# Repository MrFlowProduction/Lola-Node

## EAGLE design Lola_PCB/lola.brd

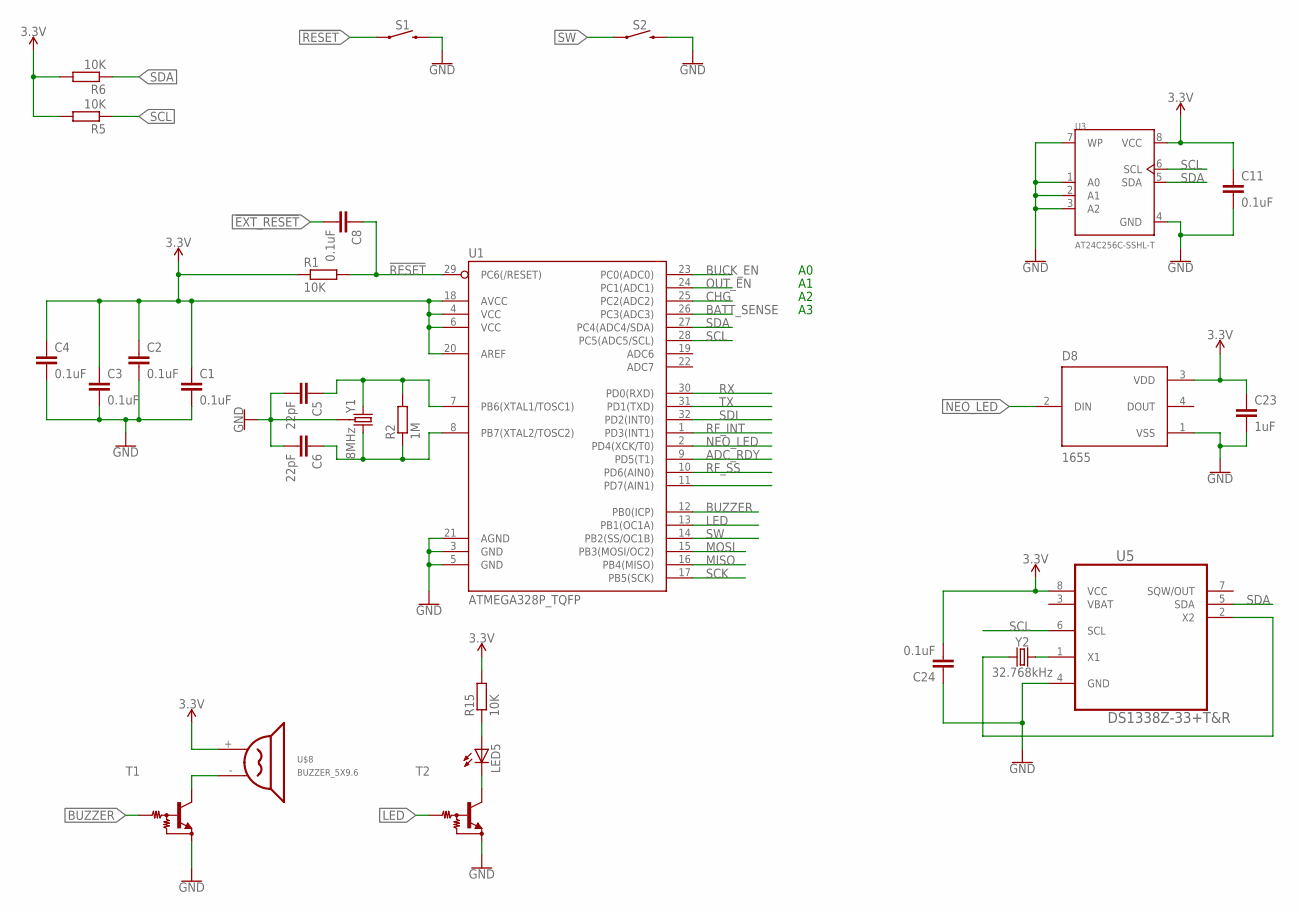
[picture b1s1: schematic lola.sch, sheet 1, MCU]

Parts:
C1, C2, C3, C4, C8, C11, C24: 0.1uF; C0603
C5, C6: 22pF; C0603
C23: 1uF; C0603
D8: 1655; LED_1655
LED5: LEDCHIPLED_0805; CHIPLED_0805
R1, R5, R6, R15: 10K; R0603
R2: 1M; R0603
S1, S2: MOMENTARY-SWITCH-SPST-SMD-4.6X2.8MM; TACTILE_SWITCH_SMD_4.6X2.8MM
T1, T2: MUN2211T1-NPN_DRIVER-SC59-BEC; SC59-BEC
U1: ATMEGA328P_TQFP; TQFP32-08
U3: AT24C256C-SSHL-T; SOIC127P600X175-8N
U5: DS1338Z-33+T&R; SOIC127P600X175-8N
U$8: BUZZER_5X9.6
Y1: 8MHz; CRYSTAL-SMD-5X3.2-4PAD
Y2: 32.768kHz; CRYSTAL-SMD-3.2X1.5MM

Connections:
3.3V: C1.1, C2.1, C3.1, C4.1, C11.1, C23.1, C24.2, D8.3 (VDD), R1.1, R5.2, R6.2, R15.2, U1.4 (VCC), U1.6 (VCC), U1.18 (AVCC), U1.20 (AREF), U3.8 (VCC), U5.8 (VCC), U$8.+ (VCC); also elsewhere on the board
!EXT_RESET: C8.2; also elsewhere on the board
!RESET: C8.1, R1.2, S1.1, S1.2 (1), U1.29 (PC6(/RESET)); also elsewhere on the board
ADC_RDY: U1.9 (PD5(T1)); also elsewhere on the board
BATT_SENSE: U1.26 (PC3(ADC3)); also elsewhere on the board
BUCK_EN: U1.23 (PC0(ADC0)); also elsewhere on the board
BUZZER: T1.B, U1.12 (PB0(ICP))
CHG: U1.25 (PC2(ADC2)); also elsewhere on the board
GND: C1.2, C2.2, C3.2, C4.2, C5.2, C6.2, C11.2, C23.2, C24.1, D8.1 (VSS), S1.3 (2), S1.4 (2), S2.3 (2), S2.4 (2), T1.E, T2.E, U1.3 (GND), U1.5 (GND), U1.21 (AGND), U3.1 (A0), U3.2 (A1), U3.3 (A2), U3.4 (GND), U3.7 (WP), U5.4 (GND), Y1.2 (3), Y1.4 (3); also elsewhere on the board
LED: T2.B, U1.13 (PB1(OC1A))
MISO: U1.16 (PB4(MISO)); also elsewhere on the board
MOSI: U1.15 (PB3(MOSI/OC2)); also elsewhere on the board
unnamed: LED5.A, R15.1
unnamed: U5.1 (X1), Y2.P$2 (2)
unnamed: U5.2 (X2), Y2.P$1 (1)
unnamed: LED5.C, T2.C
unnamed: T1.C, U$8.- (GND)
unnamed: C5.1, R2.2, U1.7 (PB6(XTAL1/TOSC1)), Y1.3 (1)
unnamed: C6.1, R2.1, U1.8 (PB7(XTAL2/TOSC2)), Y1.1 (2)
NEO_LED: D8.2 (DIN), U1.2 (PD4(XCK/T0))
OUT_EN: U1.24 (PC1(ADC1)); also elsewhere on the board
RF_INT: U1.1 (PD3(INT1)); also elsewhere on the board
RF_SS: U1.10 (PD6(AIN0)); also elsewhere on the board
RX: U1.30 (PD0(RXD)); also elsewhere on the board
SCK: U1.17 (PB5(SCK)); also elsewhere on the board
SCL: R5.1, U1.28 (PC5(ADC5/SCL)), U3.6 (SCL), U5.6 (SCL); also elsewhere on the board
SDA: R6.1, U1.27 (PC4(ADC4/SDA)), U3.5 (SDA), U5.5 (SDA); also elsewhere on the board
SDI: U1.32 (PD2(INT0)); also elsewhere on the board
SW: S2.1, S2.2 (1), U1.14 (PB2(SS/OC1B))
TX: U1.31 (PD1(TXD)); also elsewhere on the board
VBAT: U5.3 (VBAT)

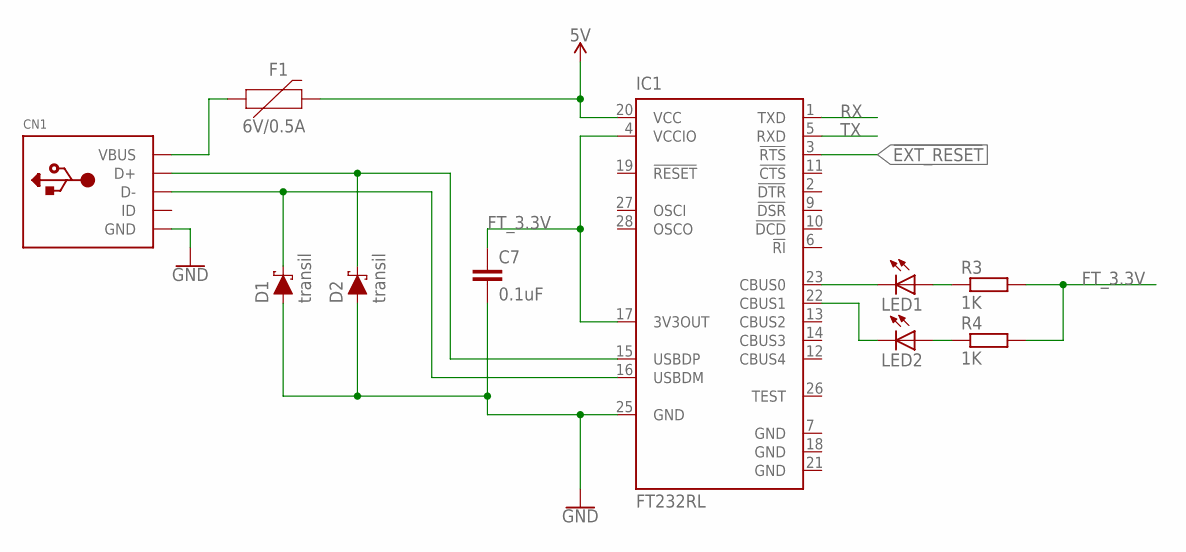
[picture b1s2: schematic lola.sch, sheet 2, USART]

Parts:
C7: 0.1uF; C0603
CN1: USBMINIB; USB-MINIB
D1, D2: transil; SOD-323
F1: 6V/0.5A; 1206
IC1: FT232RL; SSOP28
LED1, LED2: LEDCHIPLED_0805; CHIPLED_0805
R3, R4: 1K; R0603

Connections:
5V: F1.2, IC1.20 (VCC); also elsewhere on the board
!EXT_RESET: IC1.3 (!RTS); also elsewhere on the board
FT_3.3V: C7.1, IC1.4 (VCCIO), IC1.17 (3V3OUT), R3.2, R4.2
GND: C7.2, CN1.GND, D1.A, D2.A, IC1.7 (GND), IC1.18 (GND), IC1.21 (GND), IC1.25 (GND); also elsewhere on the board
unnamed: CN1.VBUS, F1.1
unnamed: CN1.D+, D2.C, IC1.15 (USBDP)
unnamed: CN1.D-, D1.C, IC1.16 (USBDM)
unnamed: LED2.A, R4.1
unnamed: IC1.22 (CBUS1), LED2.C
unnamed: IC1.23 (CBUS0), LED1.C
unnamed: LED1.A, R3.1
RX: IC1.1 (TXD); also elsewhere on the board
TX: IC1.5 (RXD); also elsewhere on the board

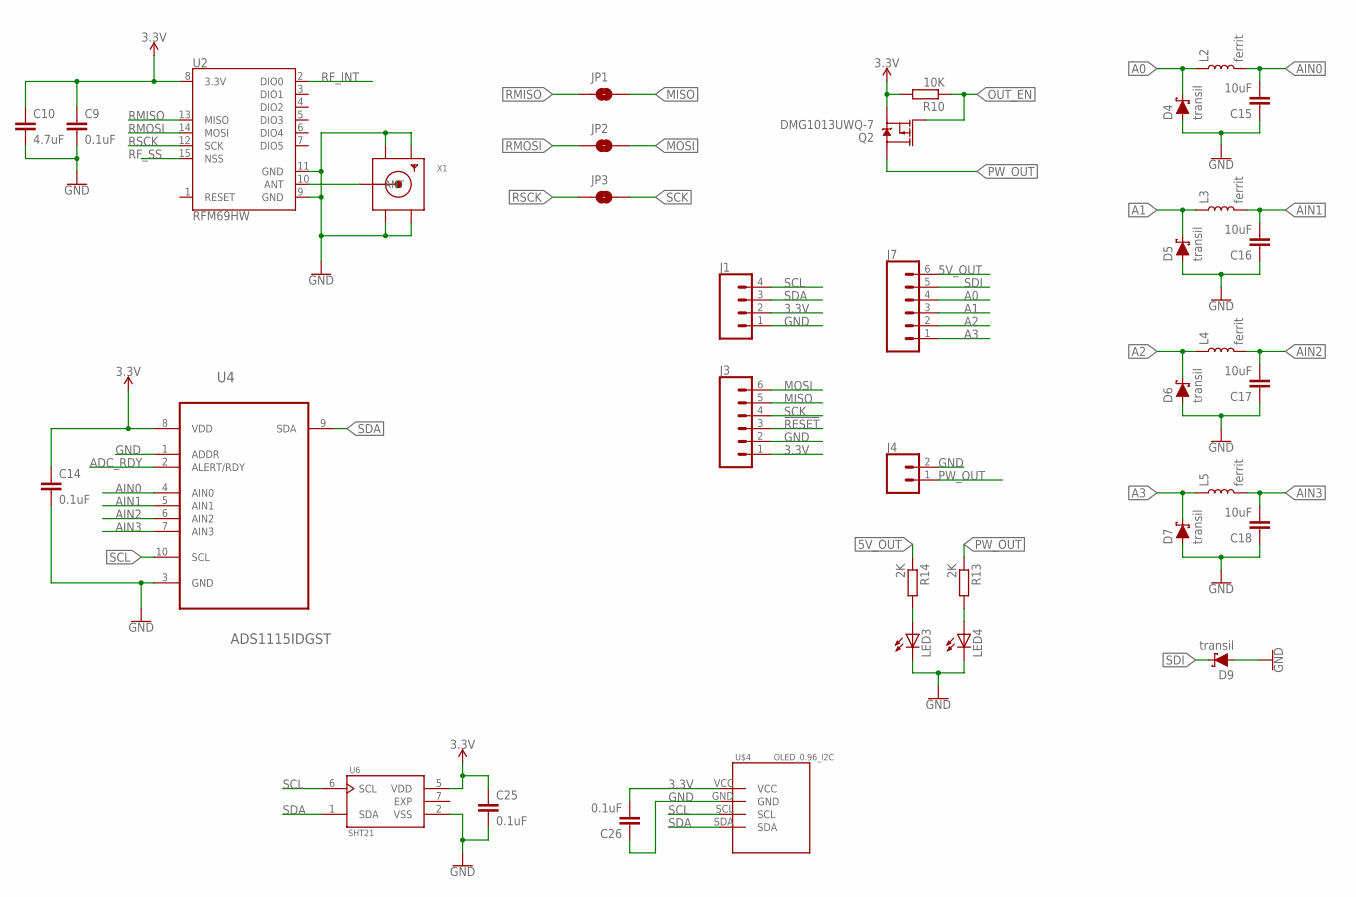
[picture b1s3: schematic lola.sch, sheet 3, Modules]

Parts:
C9, C14, C25, C26: 0.1uF; C0603
C10: 4.7uF; C0603
C15, C16, C17, C18: 10uF; C0603
D4, D5, D6, D7, D9: transil; SOD-323
J1: CONN_04LOCK_LONGPADS; 1X04_LOCK_LONGPADS
J3: CONN_06NO_SILK_FEMALE_PTH; 1X06_NO_SILK
J4: CONN_025MM; SCREWTERMINAL-5MM-2
J7: CONN_063.5MM-6; SCREWTERMINAL-3.5MM-6
JP1, JP2, JP3: JUMPER-SMT_2_NO_NO-SILK; SMT-JUMPER_2_NO_NO-SILK
L2, L3, L4, L5: ferrit; 0603
LED3, LED4: LEDCHIPLED_0805; CHIPLED_0805
Q2: DMG1013UWQ-7; SOT23-3
R10: 10K; R0603
R13, R14: 2K; R0603
U2: RFM69HW; RFM69W-XXXS2
U4: ADS1115IDGST; SOP50P490X110-10N
U6: SHT21; SON100P300X300X110-7N
U$4: OLED_0.96_I2C
X1: SMACONNECTOR_EDGE_UFL; SMA_EDGELAUNCH_UFL

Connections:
3.3V: C9.1, C10.1, C14.1, C25.1, C26.2, J1.2, J3.1, Q2.2 (S), R10.2, U2.8 (3.3V), U4.8 (VDD), U6.5 (VDD), U$4.VCC; also elsewhere on the board
5V_OUT: J7.6, R14.1; also elsewhere on the board
!RESET: J3.3; also elsewhere on the board
A0: D4.C, J7.4, L2.1
A1: D5.C, J7.3, L3.1
A2: D6.C, J7.2, L4.1
A3: D7.C, J7.1, L5.1
ADC_RDY: U4.2 (ALERT/RDY); also elsewhere on the board
AIN0: C15.2, L2.2, U4.4 (AIN0)
AIN1: C16.2, L3.2, U4.5 (AIN1)
AIN2: C17.2, L4.2, U4.6 (AIN2)
AIN3: C18.2, L5.2, U4.7 (AIN3)
EXP: U6.7 (EXP)
GND: C9.2, C10.2, C14.2, C15.1, C16.1, C17.1, C18.1, C25.2, C26.1, D4.A, D5.A, D6.A, D7.A, D9.A, J1.1, J3.2, J4.2, LED3.C, LED4.C, U2.9 (GND), U2.11 (GND), U4.1 (ADDR), U4.3 (GND), U6.2 (VSS), U$4.GND, X1.GND@1 (GND1), X1.GND@2 (GND2), X1.GND@3 (GND3), X1.GND@4 (GND4); also elsewhere on the board
MISO: J3.5, JP1.2; also elsewhere on the board
MOSI: J3.6, JP2.2; also elsewhere on the board
unnamed: U2.10 (ANT), X1.P (ANT)
unnamed: LED3.A, R14.2
unnamed: LED4.A, R13.2
OUT_EN: Q2.1 (G), R10.1; also elsewhere on the board
PW_OUT: J4.1, Q2.3 (D), R13.1
RF_INT: U2.2 (DIO0); also elsewhere on the board
RF_SS: U2.15 (NSS); also elsewhere on the board
RMISO: JP1.1, U2.13 (MISO)
RMOSI: JP2.1, U2.14 (MOSI)
RSCK: JP3.1, U2.12 (SCK)
SCK: J3.4, JP3.2; also elsewhere on the board
SCL: J1.4, U4.10 (SCL), U6.6 (SCL), U$4.SCL; also elsewhere on the board
SDA: J1.3, U4.9 (SDA), U6.1 (SDA), U$4.SDA; also elsewhere on the board
SDI: D9.C, J7.5; also elsewhere on the board

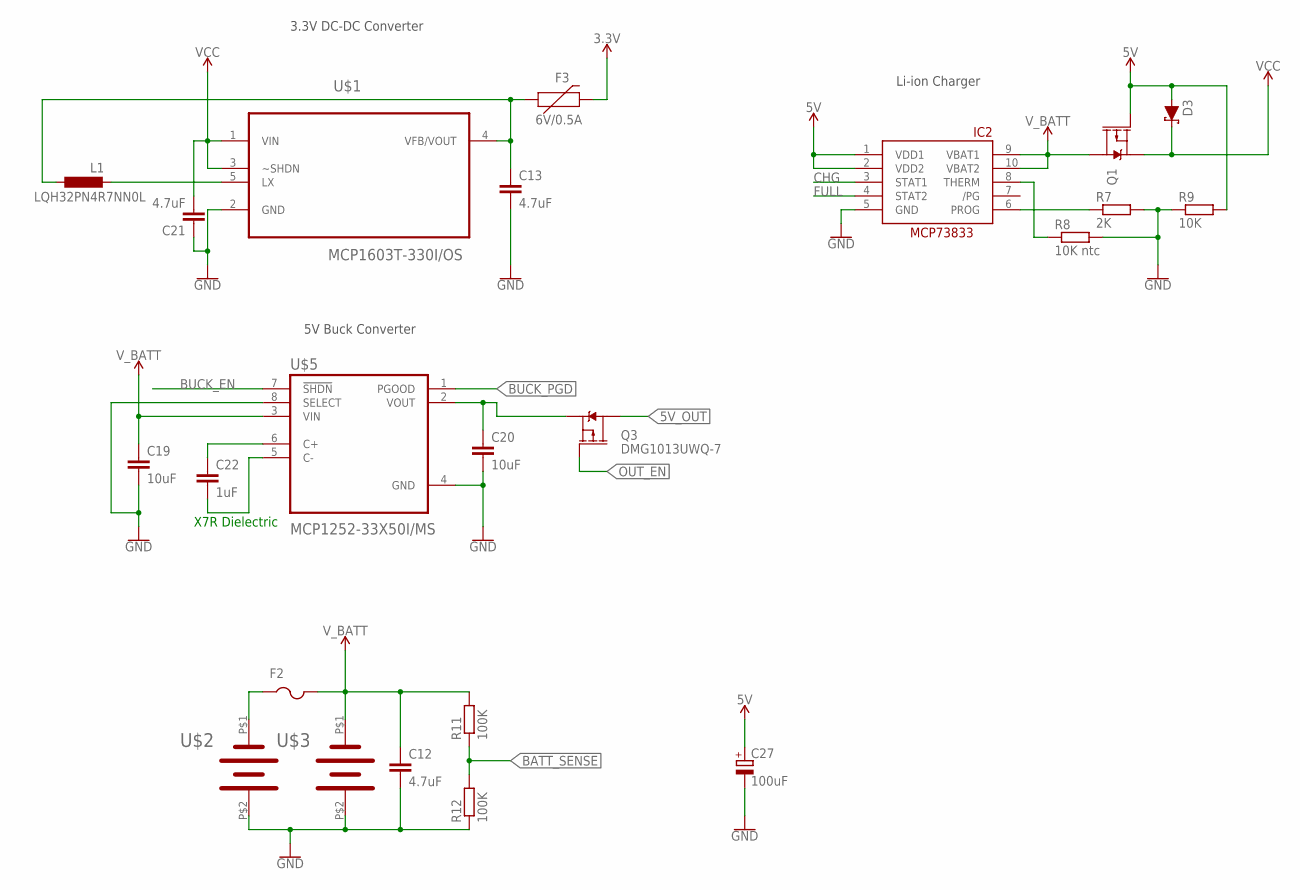
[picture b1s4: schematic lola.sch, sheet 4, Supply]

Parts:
C12: 4.7uF; C0603
C13, C21: 4.7uF; C1206
C19, C20: 10uF; C1206
C22: 1uF; C0805
C27: 100uF; CT6032
D3: DIODE-SCHOTTKY-B340A; SMA-DIODE
F2: PTCFUSE-1812; 1812
F3: 6V/0.5A; 1206
IC2: MCP73833-UN; MSOP10
L1: LQH32PN4R7NN0L; L1812
Q1: MOSFET_PCH-DMG2307L; SOT23-3
Q3: DMG1013UWQ-7; SOT23-3
R7: 2K; R0603
R8: 10K ntc; R0603
R9: 10K; R0603
R11, R12: 100K; R0603
U$1: MCP1603T-330I/OS; SOT95P280X110-5N
U$2, U$3: COMF_BHC-18650-1P; MR18650_HOLDER
U$5: MCP1252-33X50I/MS; SOP65P490X110-8N

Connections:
3.3V: F3.2; also elsewhere on the board
5V: C27.- (+), D3.A, IC2.1 (VDD1), IC2.2 (VDD2), Q1.1 (G), R9.2; also elsewhere on the board
5V_OUT: Q3.3 (D); also elsewhere on the board
BATT_SENSE: R11.1, R12.2; also elsewhere on the board
BUCK_EN: U$5.7 (!SHDN); also elsewhere on the board
BUCK_PGD: U$5.1 (PGOOD)
CHG: IC2.3 (STAT1); also elsewhere on the board
FULL: IC2.4 (STAT2)
GND: C12.2, C13.2, C19.2, C20.2, C21.1, C27.+ (-), IC2.5 (GND), R7.2, R8.2, R9.1, R12.1, U$1.2 (GND), U$2.P$2 (GND), U$3.P$2 (GND), U$5.4 (GND), U$5.8 (SELECT); also elsewhere on the board
unnamed: F2.1, U$2.P$1 (BAT)
unnamed: C13.1, F3.1, L1.1, U$1.4 (VFB/VOUT)
unnamed: IC2.8 (THERM), R8.1
unnamed: IC2.6 (PROG), R7.1
unnamed: L1.2, U$1.5 (LX)
unnamed: C20.1, Q3.2 (S), U$5.2 (VOUT)
unnamed: C22.1, U$5.6 (C+)
unnamed: C22.2, U$5.5 (C-)
OUT_EN: Q3.1 (G); also elsewhere on the board
VCC: C21.2, D3.C, Q1.2 (S), U$1.1 (VIN), U$1.3 (~SHDN)
V_BATT: C12.1, C19.1, F2.2, IC2.9 (VBAT1), IC2.10 (VBAT2), Q1.3 (D), R11.2, U$3.P$1 (BAT), U$5.3 (VIN)

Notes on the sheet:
X7R Dielectric
3.3V DC-DC Converter
5V Buck Converter
Li-ion Charger

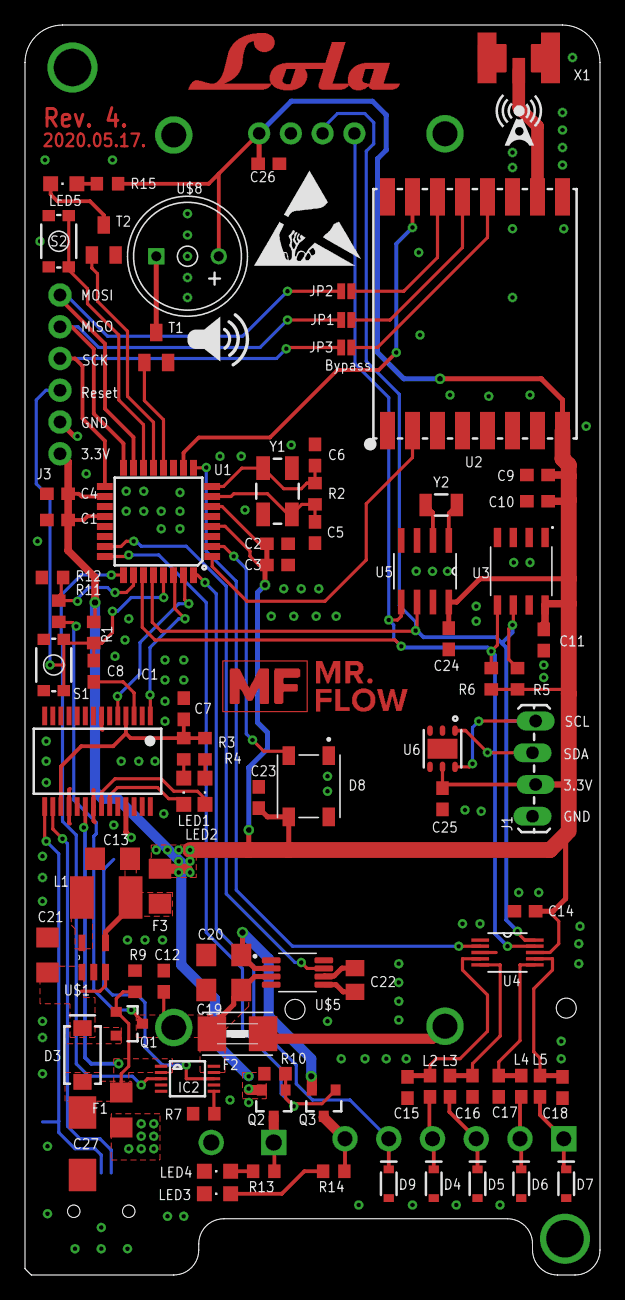
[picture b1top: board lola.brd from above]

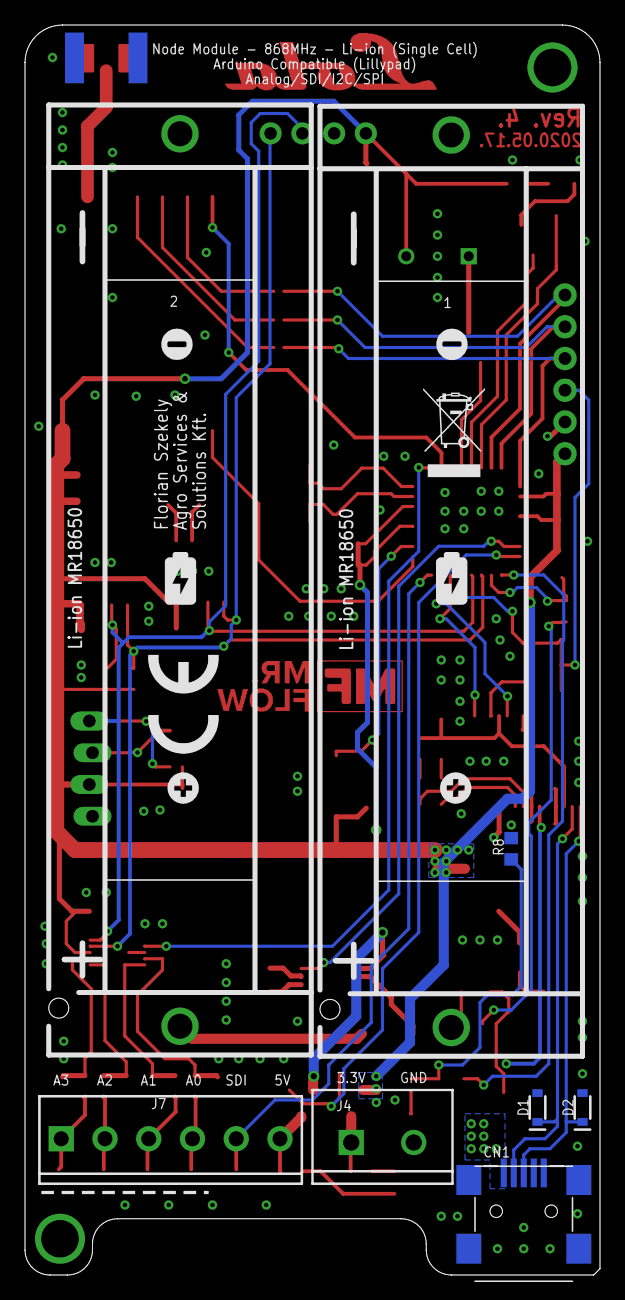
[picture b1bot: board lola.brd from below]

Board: 2 copper layers, 46.0 x 100.0 mm, 110 parts (16 on the bottom side), 65 nets.

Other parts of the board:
U$6: LOLA_LOGO_LAYER
U$7: MRFLOW
U$9: RADIO_LOGO
U$10, U$15: MINUS_LOGO
U$11: ESD_LOGO
U$12: TONNE_LOGO
U$13: AGRO_SMALL_LOGO
U$14: SOUND_ICON
U$16, U$17: PLUS_LOGO
U$18, U$19: BATTERY_LOGO
U$20: CE_LOGO

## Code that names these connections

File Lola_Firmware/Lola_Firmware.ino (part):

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#define LED               9         // Stat LED pin
#define BATT_VOLTAGE      A3        // Battery Voltage sense pin (analog)
#define SUPPLY_EN         A1        // Sensors supply enable pin
#define RF_INT            3         // RF module interrupt pin
#define RF_SS             6         // RF module slave select pin
#define SDI               2         // SDI-12 Bus pin
#define ADC_RDY           5         // ADC Ready pin
#define NEO_LED           4         // Neo Pixel led output
#define BUZZER            8         // Buzzer output
#define BUTTON            10        // User Button input
#define CHARGE            A2        // Battery charge status input
#define BUCK_EN           A0        // 5V Buck Boost supply enable
//========================================================================


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#define ADC_POWERUP_TIME      200                   // ADC inputs power up wait time
#define STAT_INTERVAL         200                   // LED Blink Interval (ms)
#define RESET_INTERVAL        960                   // Hágy alvás ciklus után resetelje magát az eszközt (960 az kb 2 naponta 3 perces időzítéssel)
#define SDI_RDY_TIME          3000                  // SDI-12 busz powerup sensor time
#define NEO_BRIGHT            30                    // NEO led max bright
#define SDI_TIMEOUT           1000                  // SDI szenzor válasz időkorlát
// =============================================================================================


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    // Supply Power OFF
    pinMode(SUPPLY_EN, OUTPUT);
    digitalWrite(SUPPLY_EN, LOW);
    pinMode(BUCK_EN, OUTPUT);
    digitalWrite(BUCK_EN, HIGH);
    delay(ADC_POWERUP_TIME);
  }
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    digitalWrite(BUCK_EN, LOW);
    delay(100);
    pinMode(SUPPLY_EN, INPUT);
    pinMode(BUCK_EN, INPUT);
  }

  printdone();
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
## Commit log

2020-09-10 PCB Desing

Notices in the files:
parts and their libraries:
SparkFun-IC-Microcontroller: Licensing: Creative Commons ShareAlike 4.0 International - https://creativecommons.org/licenses/by-sa/4.0
